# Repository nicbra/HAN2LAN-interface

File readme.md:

# HAN-to-WLAN interface module
This is a hardware project where the readings of electrical power-meters will be interfaced for logging and display without further interaction with external servers and third-party vendors.

## Hardware
The hardware-module are developed with the Aidon-meters in mind, which is the most used power-meter in eastern Norway.
The hardware-module is a standalone module powered by the HAN-port of the AMS-meter without the neccesity of external power supply. For Aidon, there is a maximum current delivery of 30 mA, which is the highest ammount among the AMS-vendors used in Norway.

## Data parsing
This repository contains only the hardware. You can either write your own firmware for the ESP8266, but I recommend using [AmsToMqttBridge](https://github.com/gskjold/AmsToMqttBridge) from GSkjold.

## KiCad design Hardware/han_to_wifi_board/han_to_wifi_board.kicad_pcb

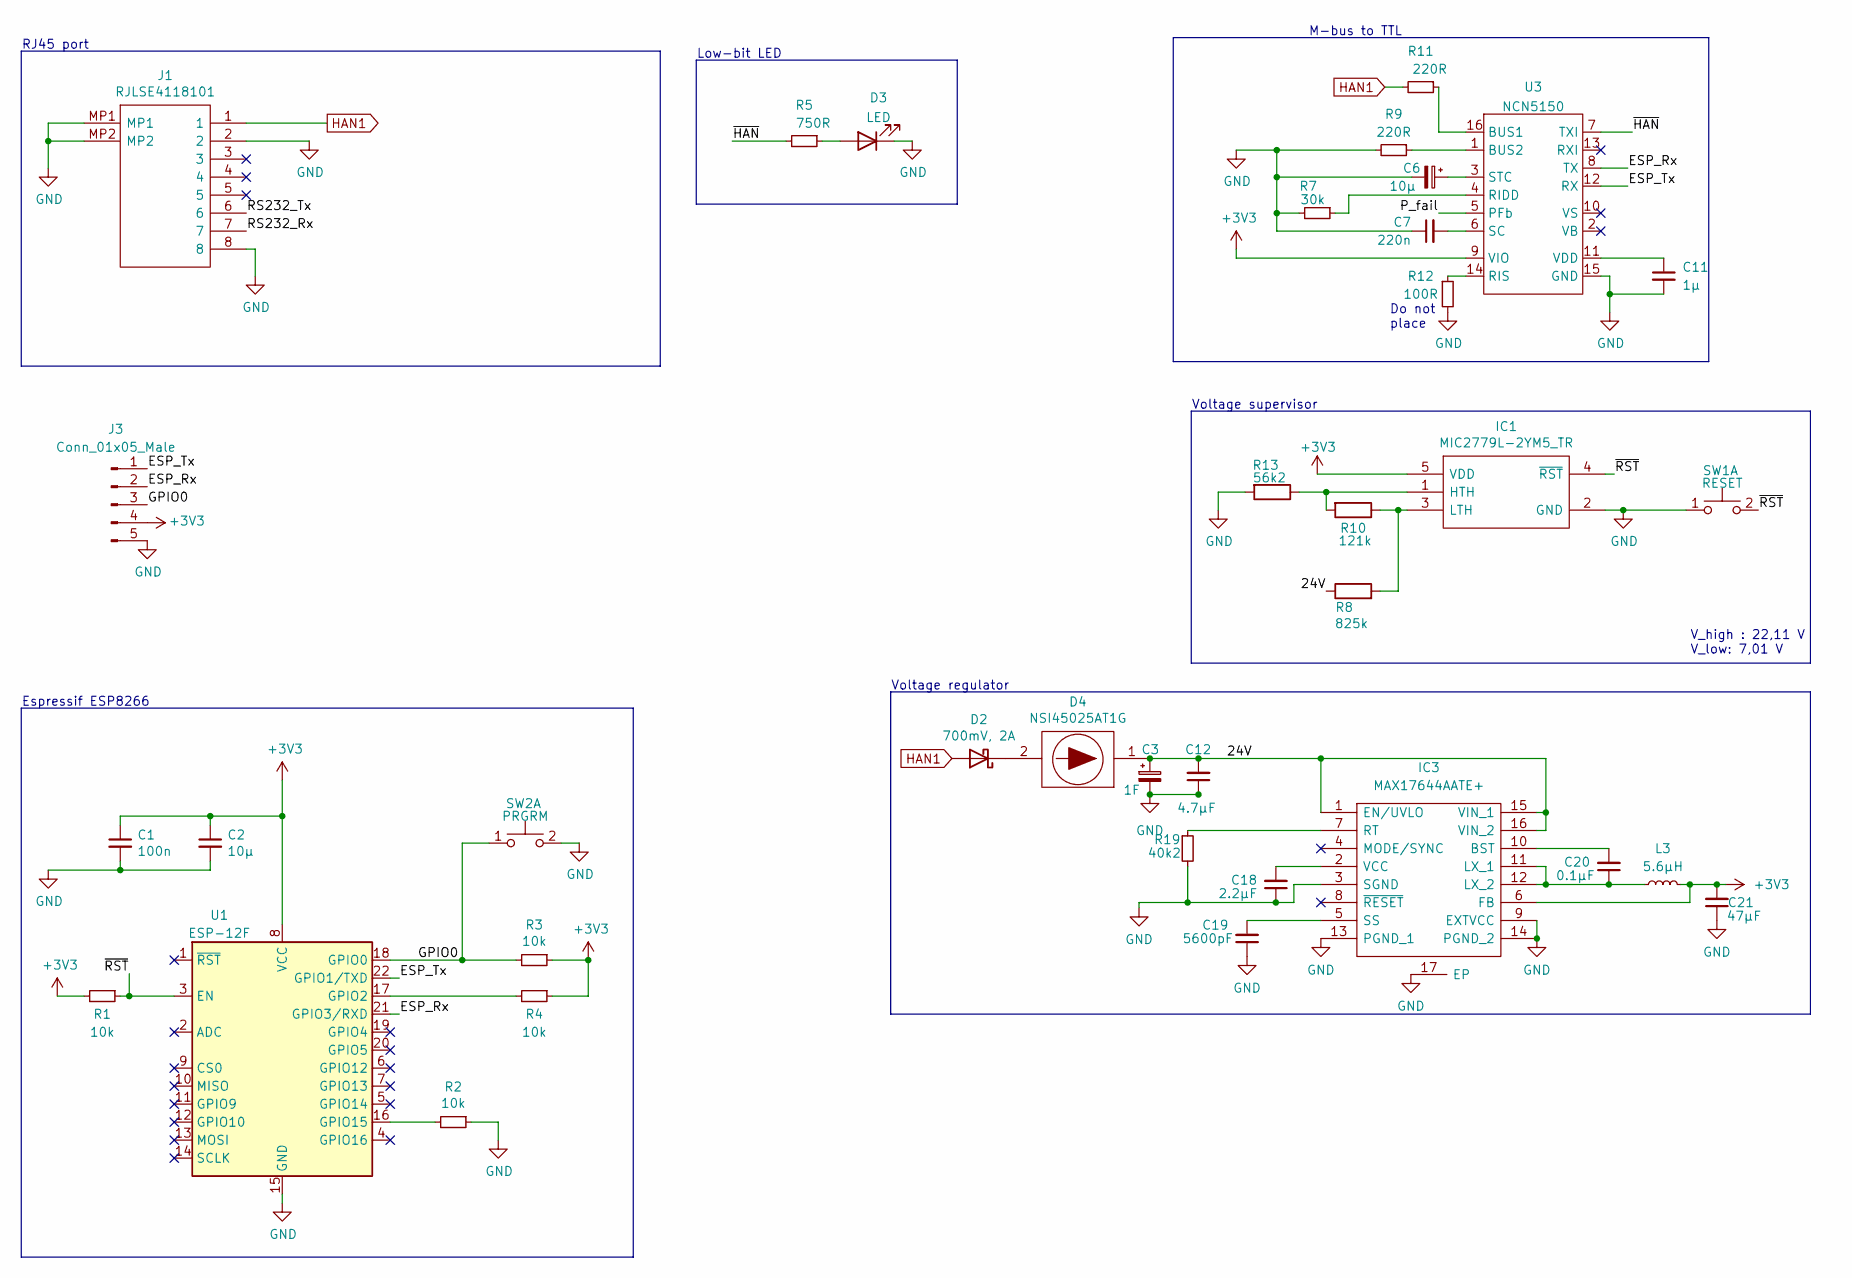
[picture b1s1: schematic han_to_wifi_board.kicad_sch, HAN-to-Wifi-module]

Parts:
C1: 100n; C_0603_1608Metric
C2, C6: 10µ; C_0603_1608Metric
C3: 1F; MAL202117102E3
C7: 220n; C_0603_1608Metric
C11: 1µ; C_0805_2012Metric
C12: 4.7µF; C_0805_2012Metric
C18: 2.2µF; C_0603_1608Metric
C19: 5600pF; C_0603_1608Metric
C20: 0.1µF; C_0603_1608Metric
C21: 47µF; C_0805_2012Metric
D2: 700mV, 2A; D_SMA
D3: LED; LED_0603_1608Metric
D4: NSI45025AT1G; Manufacturer_Part_Number NSI45025AT1G; Mouser Part Number 863-NSI45025AT1G
IC1: MIC2779L-2YM5_TR; SOT95P280X145-5N; Manufacturer_Part_Number MIC2779L-2YM5 TR
IC3: MAX17644AATE+; QFN50P300X300X80-17N; Manufacturer_Part_Number MAX17644AATE+; Mouser Part Number 700-MAX17644AATE+
J1: RJLSE4118101; Manufacturer_Part_Number RJLSE4118101; Mouser Part Number 523-RJLSE4118101
J3: Conn_01x05_Male; Molex_PicoBlade_53261-0571_1x05-1MP_P1.25mm_Horizontal
L3: 5.6µH; L_Vishay_IHLP-2020
R1, R2, R3, R4: 10k; R_0603_1608Metric
R5: 750R; R_0603_1608Metric
R7: 30k; R_0603_1608Metric
R8: 825k; R_0603_1608Metric
R9, R11: 220R; R_0603_1608Metric
R10: 121k; R_0603_1608Metric
R12: 100R; R_0603_1608Metric
R13: 56k2; R_0603_1608Metric
R19: 40k2; R_0603_1608Metric
SW1: RESET; EVQP2
SW2: PRGRM; EVQP2
U1: ESP-12F; ESP-12E
U3: NCN5150; SOIC127P600X175-16N

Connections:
+3V3: C1.1, C2.1, C21.2, IC1.5 (VDD), IC3.6 (FB), J3.4, L3.2, R1.2, R3.1, R4.1, U1.8 (VCC), U3.9 (VIO)
/24V: C3.1, C12.2, D4.1, IC3.1 (EN/UVLO), IC3.15 (VIN_1), IC3.16 (VIN_2), R8.1
/ESP_Rx: J3.2, U1.21 (GPIO3/RXD), U3.8 (TX)
/ESP_Tx: J3.1, U1.22 (GPIO1/TXD), U3.12 (RX)
/GPIO0: J3.3, R3.2, SW2.1 (C), U1.18 (GPIO0)
/P_fail: U3.5 (PFb)
/RS232_Rx: J1.7
/RS232_Tx: J1.6
/~HAN: R5.2, U3.7 (TXI)
/~RST: IC1.4 (~RST), R1.1, SW1.2 (D), U1.3 (EN)
GND: C1.2, C2.2, C3.2, C6.2, C7.1, C11.2, C12.1, C18.1, C19.1, C21.1, D3.1 (K), IC1.2 (GND), IC3.3 (SGND), IC3.9 (EXTVCC), IC3.13 (PGND_1), IC3.14 (PGND_2), IC3.17 (EP), J1.2, J1.8, J1.MP1, J1.MP2, J3.5, R2.1, R7.2, R9.2, R12.2, R13.2, R19.2, SW1.1 (C), SW2.2 (D), U1.15 (GND), U3.15 (GND)
HAN1: D2.2 (A), J1.1, R11.2
unnamed: C6.1, U3.3 (STC)
unnamed: C7.2, U3.6 (SC)
unnamed: C11.1, U3.11 (VDD)
unnamed: C18.2, IC3.2 (VCC)
unnamed: C19.2, IC3.5 (SS)
unnamed: C20.1, IC3.11 (LX_1), IC3.12 (LX_2), L3.1
unnamed: C20.2, IC3.10 (BST)
unnamed: D2.1 (K), D4.2
unnamed: D3.2 (A), R5.1
unnamed: IC1.1 (HTH), R10.2, R13.1
unnamed: IC1.3 (LTH), R8.2, R10.1
unnamed: IC3.7 (RT), R19.1
unnamed: R2.2, U1.16 (GPIO15)
unnamed: R4.2, U1.17 (GPIO2)
unnamed: R7.1, U3.4 (RIDD)
unnamed: R9.1, U3.1 (BUS2)
unnamed: R11.1, U3.16 (BUS1)
unnamed: R12.1, U3.14 (RIS)

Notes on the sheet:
Espressif ESP8266
M-bus to TTL
Voltage regulator
Do not place
Voltage supervisor
RJ45 port
Low-bit LED
V_high : 22,11 V V_low: 7,01 V

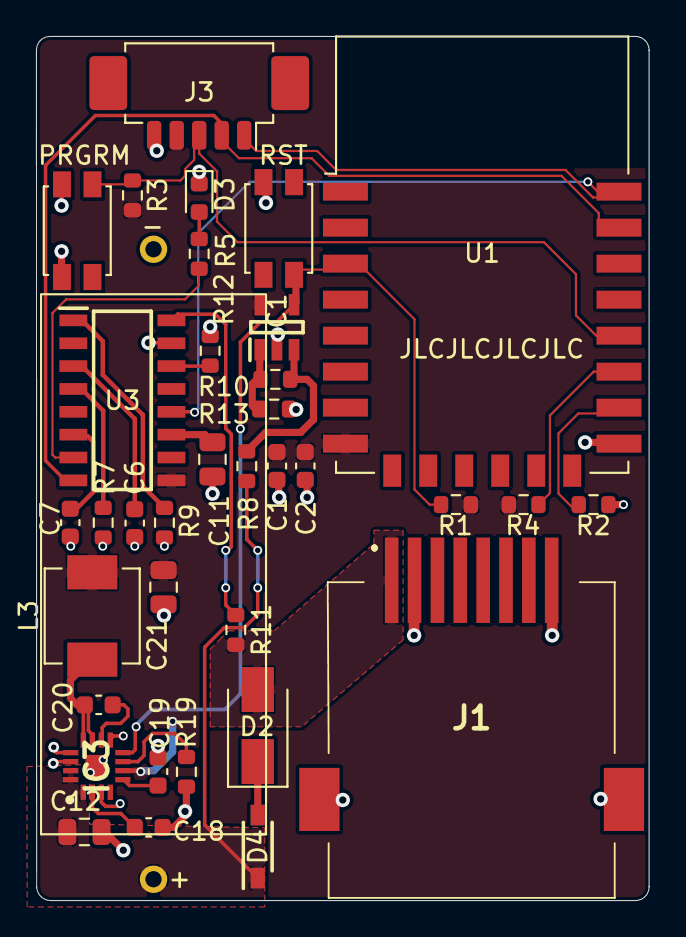
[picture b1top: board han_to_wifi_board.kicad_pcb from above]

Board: 2 copper layers, 34.0 x 48.0 mm, 36 parts (0 on the bottom side), 27 nets.

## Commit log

2022-02-06 Moved to kicad6 and finished board
2022-05-04 New buck converter
2022-05-14 Added BOM
2022-05-14 Initialized platformio
2022-05-18 Connected SGND on buck to GND
2022-08-10 Reset pin on buck
2022-09-13 September hw changes
2023-01-15 Changes after first bringup
2023-01-15 Deleted datasheet
